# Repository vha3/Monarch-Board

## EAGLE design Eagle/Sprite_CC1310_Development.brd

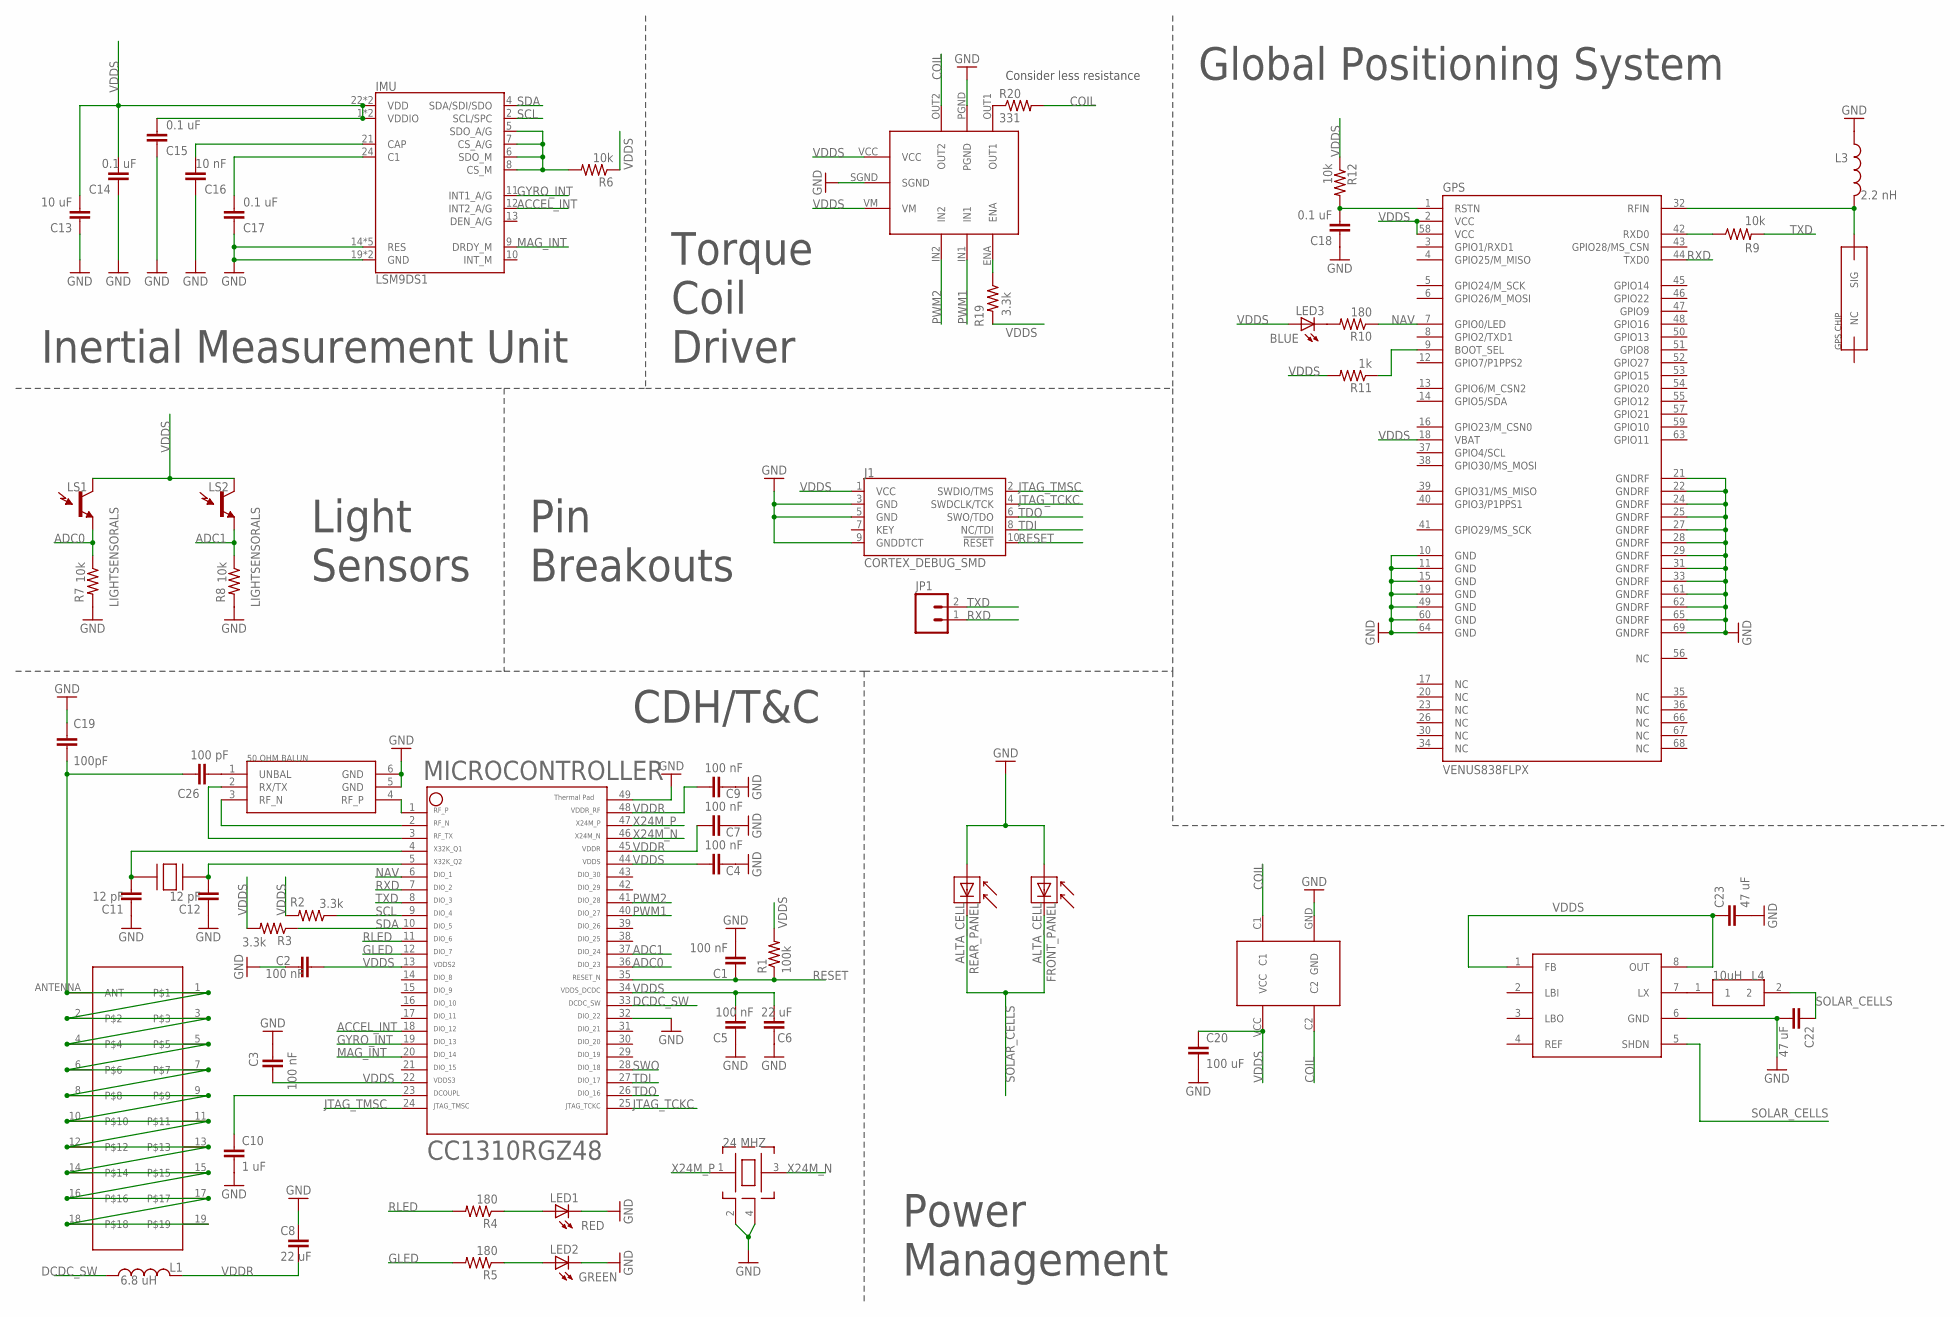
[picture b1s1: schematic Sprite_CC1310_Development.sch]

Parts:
32.768: FC-135
BALUN: JOHANSON_BALUN
C1, C2, C3, C4, C5, C7, C9: 100 nF; 0402-CAP
C6, C8: 22 uF; 0402-CAP
C10: 1 uF; 0402-CAP
C11, C12: 12 pF; 0402-CAP
C13: 10 uF; 0402-CAP
C14, C15, C17, C18: 0.1 uF; 0402-CAP
C16: 10 nF; 0402-CAP
C19: 100pF; 0603-CAP
C20: 100 uF; 0805
C22, C23: 47 uF; 0805
C26: 100 pF; 0402-CAP
FRONT_PANEL: ALTA_CELL
GPS: VENUS838FLPX
IMU: LSM9DS1; LGA24-8X4
J1: CORTEX_DEBUG_SMD; SAMTECH_FTSH-105-01
JP1: M02PTH; 1X02
L1: 6.8 uH; 0603
L3: 2.2 nH; 0603
L4: 10uH; ASPI-0315FS
LED1: RED; LED-0603
LED2: GREEN; LED-0603
LED3: BLUE; LED-0603
LS1, LS2: LIGHTSENSORALS; ALS-PT19
MICROCONTROLLER: CC1310
R1: 100k; 0402-RES
R2, R3, R19: 3.3k; 0402-RES
R4, R5, R10: 180; 0402-RES
R6, R7, R8, R9, R12: 10k; 0402-RES
R11: 1k; 0402-RES
R20: 331; 0402-RES
REAR_PANEL: ALTA_CELL
TSX3225: TSX-3225
U$2: LV8417CS
U$4: PANASONIC_RECTIFIER
U$5: JOHANSON_GPS_CHIP
U$6: PCB_ANTENNA
U$8: L6920

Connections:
ACCEL_INT: IMU.12 (INT2_A/G), MICROCONTROLLER.18
ADC0: LS1.E (E1), MICROCONTROLLER.36, R7.1
ADC1: LS2.E (E1), MICROCONTROLLER.37, R8.1
ANTENNA: C19.2, C26.1, U$6.1, U$6.2, U$6.3, U$6.4, U$6.5, U$6.6, U$6.7, U$6.8, U$6.9, U$6.10, U$6.11, U$6.12, U$6.13, U$6.14, U$6.15, U$6.16, U$6.17, U$6.18, U$6.19, U$6.ANTENNA (ANT)
COIL: R20.2, U$2.OUT2, U$4.C1, U$4.C2
DCDC_SW: L1.1, MICROCONTROLLER.33
GLED: MICROCONTROLLER.12, R5.2
GND: BALUN.5 (GND), BALUN.6 (GND), C1.2, C2.2, C3.2, C4.2, C5.2, C6.2, C7.2, C8.2, C9.2, C10.2, C11.2, C12.2, C13.2, C14.2, C15.2, C16.2, C17.2, C18.2, C19.1, C20.2, C22.2, C23.2, FRONT_PANEL.-, GPS.10 (GND), GPS.11 (GND), GPS.15 (GND), GPS.19 (GND), GPS.21 (GNDRF), GPS.22 (GNDRF), GPS.24 (GNDRF), GPS.25 (GNDRF), GPS.27 (GNDRF), GPS.28 (GNDRF), GPS.29 (GNDRF), GPS.31 (GNDRF), GPS.33 (GNDRF), GPS.49 (GND), GPS.60 (GND), GPS.61 (GNDRF), GPS.62 (GNDRF), GPS.64 (GND), GPS.65 (GNDRF), GPS.69 (GNDRF), IMU.14 (RES), IMU.15 (RES), IMU.16 (RES), IMU.17 (RES), IMU.18 (RES), IMU.19 (GND), IMU.20 (GND), J1.3 (GND), J1.5 (GND), J1.9 (GNDDTCT), L3.1, LED1.C, LED2.C, MICROCONTROLLER.32, MICROCONTROLLER.49, R7.2, R8.2, REAR_PANEL.-, TSX3225.2, TSX3225.4, U$2.PGND, U$2.SGND, U$4.GND, U$8.6 (GND)
GYRO_INT: IMU.11 (INT1_A/G), MICROCONTROLLER.19
JTAG_TCKC: J1.4 (SWDCLK/TCK), MICROCONTROLLER.25
JTAG_TMSC: J1.2 (SWDIO/TMS), MICROCONTROLLER.24
MAG_INT: IMU.9 (DRDY_M), MICROCONTROLLER.20
unnamed: C10.1, MICROCONTROLLER.23
unnamed: 32.768.P2, C11.1, MICROCONTROLLER.4
unnamed: 32.768.P1, C12.1, MICROCONTROLLER.5
unnamed: LED1.A, R4.1
unnamed: LED2.A, R5.1
unnamed: IMU.5 (SDO_A/G), IMU.6 (SDO_M), IMU.7 (CS_A/G), IMU.8 (CS_M), R6.2
unnamed: GPS.42 (RXD0), R9.1
unnamed: C16.1, IMU.21 (CAP)
unnamed: C17.1, IMU.24 (C1)
unnamed: LED3.C, R10.2
unnamed: GPS.9 (BOOT_SEL), R11.1
unnamed: C18.1, GPS.1 (RSTN), R12.2
unnamed: GPS.32 (RFIN), L3.2, U$5.SIG
unnamed: R19.1, U$2.ENA
unnamed: R20.1, U$2.OUT1
unnamed: BALUN.1 (UNBAL), C26.2
unnamed: BALUN.4 (RF_P), MICROCONTROLLER.1
unnamed: BALUN.3 (RF_N), MICROCONTROLLER.2
unnamed: BALUN.2 (RX/TX), MICROCONTROLLER.3
unnamed: L4.1, U$8.7 (LX)
NAV: GPS.7 (GPIO0/LED), MICROCONTROLLER.6, R10.1
PWM1: MICROCONTROLLER.40, U$2.IN1
PWM2: MICROCONTROLLER.41, U$2.IN2
RESET: C1.1, J1.10 (!RESET), MICROCONTROLLER.35, R1.1
RLED: MICROCONTROLLER.11, R4.2
RXD: GPS.44 (TXD0), JP1.1, MICROCONTROLLER.7
SCL: IMU.2 (SCL/SPC), MICROCONTROLLER.9, R2.1
SDA: IMU.4 (SDA/SDI/SDO), MICROCONTROLLER.10, R3.1
SOLAR_CELLS: C22.1, FRONT_PANEL.+, L4.2, REAR_PANEL.+, U$8.5 (SHDN)
SWO: MICROCONTROLLER.28
TDI: J1.8 (NC/TDI), MICROCONTROLLER.27
TDO: J1.6 (SWO/TDO), MICROCONTROLLER.26
TXD: JP1.2, MICROCONTROLLER.8, R9.2
VDDR: C7.1, C8.1, C9.1, L1.2, MICROCONTROLLER.45, MICROCONTROLLER.48
VDDS: C2.1, C3.1, C4.1, C5.1, C6.1, C13.1, C14.1, C15.1, C20.1, C23.1, GPS.2 (VCC), GPS.18 (VBAT), GPS.58 (VCC), IMU.1 (VDDIO), IMU.3 (VDDIO), IMU.22 (VDD), IMU.23 (VDD), J1.1 (VCC), LED3.A, LS1.C (C1), LS2.C (C1), MICROCONTROLLER.13, MICROCONTROLLER.22, MICROCONTROLLER.34, MICROCONTROLLER.44, R1.2, R2.2, R3.2, R6.1, R11.2, R12.1, R19.2, U$2.VCC, U$2.VM, U$4.VCC, U$8.1 (FB), U$8.8 (OUT)
X24M_N: MICROCONTROLLER.46, TSX3225.3
X24M_P: MICROCONTROLLER.47, TSX3225.1

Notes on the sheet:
CDH/T&C
Inertial Measurement Unit
Power Management
Light Sensors
Global Positioning System
Pin Breakouts
Torque Coil Driver
Consider less resistance

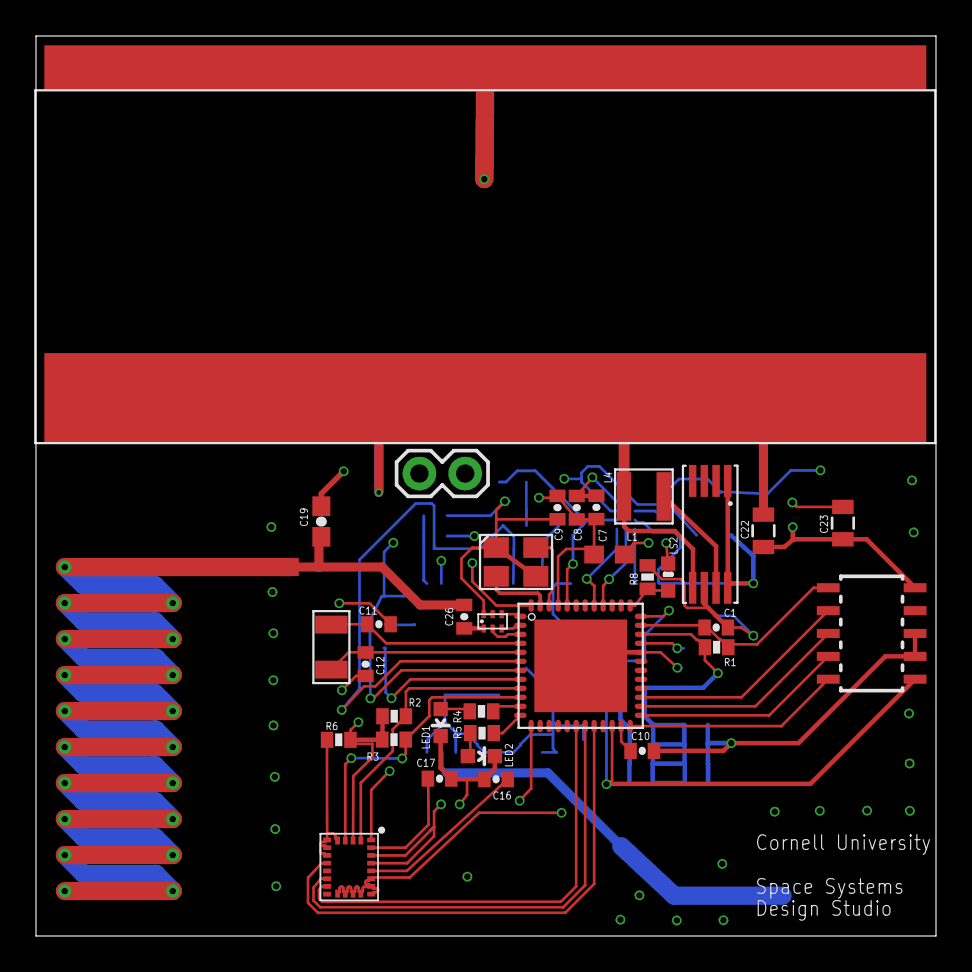
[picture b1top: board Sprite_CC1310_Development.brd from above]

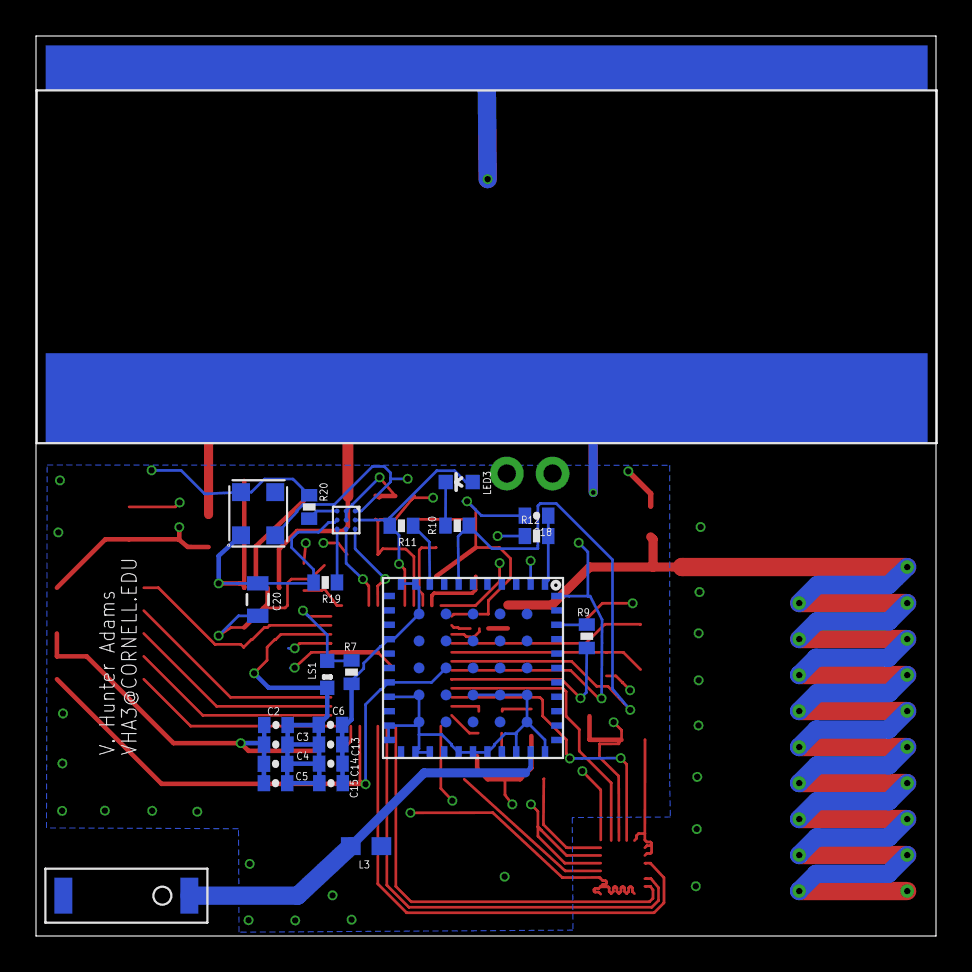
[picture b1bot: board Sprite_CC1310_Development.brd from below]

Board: 4 copper layers, 50.0 x 50.0 mm, 60 parts (26 on the bottom side), 48 nets.

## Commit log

2018-01-19 routing in progress
2018-01-19 still working
2018-01-21 still routing
2018-01-22 closer
2018-01-22 fixed antenna
2018-01-22 draft layout complete
2018-01-23 added silkscreen
2018-01-24 need new boost converter, obsolete component :(
2018-01-24 updated boost regulator
2018-01-25 cleaning up
2018-02-25 Updated matching network
2018-02-27 rearranging files
2018-02-27 small test
2018-02-27 added images
2018-02-27 cleaning
2018-02-27 readme
2018-03-08 updated BOM
2018-03-12 Fixed HDMI
2018-04-12 fixed BOM
2018-06-07 updated boost converter, eliminated unnecessary tuning components, rotated oscillator, updated solar pads
2019-01-18 still need to add breakouts
2019-01-19 board layout complete, need to update other files
2019-01-20 updated all files
2019-01-21 RFQ for BSU, changed matching circuit
2019-08-21 BSU suggestions
2019-09-08 updated JTAG and UART pinouts
2019-09-08 spec image

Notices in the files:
parts and their libraries:
SparkFun: Licensing: CC v3.0 Share-Alike You are welcome to use this library for commercial purposes.
SparkFun-Sensors: Licensing: Creative Commons ShareAlike 4.0 International - https://creativecommons.org/licenses/by-sa/4.0
